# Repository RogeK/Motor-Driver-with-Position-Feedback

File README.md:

# Motor-Driver-with-Position-Feedback
This repo contains a design for a motor driver with position feedback HAT that can be attached to the 40 GPIO pins of the Pi. It is intended to be used to track and control the instantaneous position of the M1N10FB11G Brushless DC Motor which has an incremental encoder attached to its shaft. The scenarios that the daughter board with a Pi are used in include solar tracking systems, automatic sliding gate and a hybrid engine fan.

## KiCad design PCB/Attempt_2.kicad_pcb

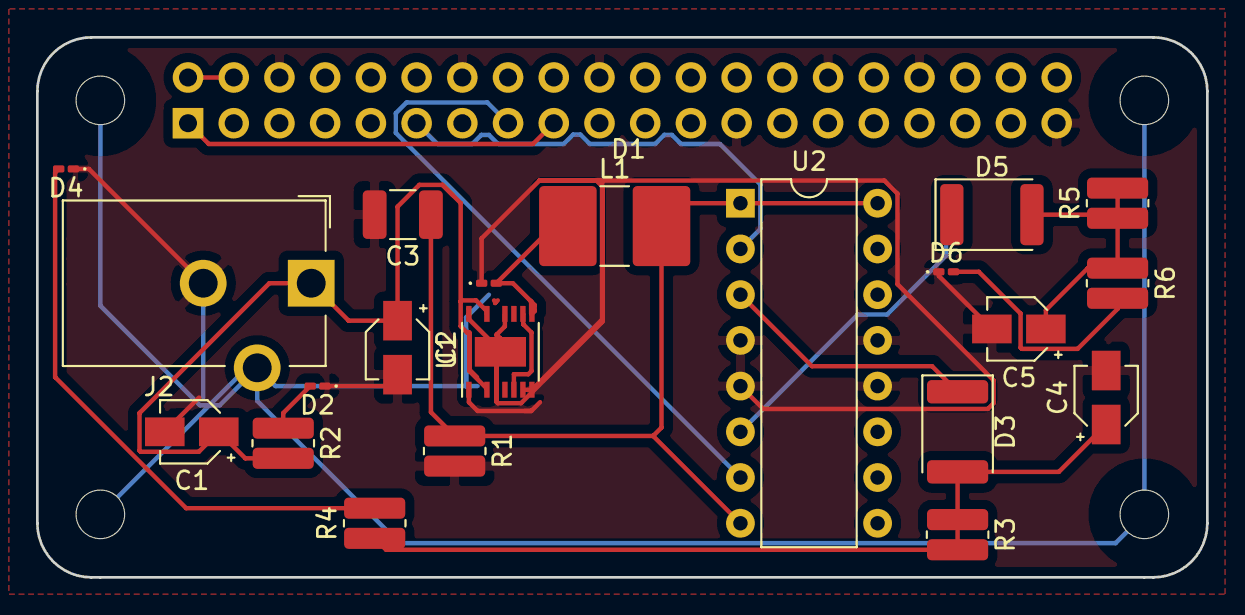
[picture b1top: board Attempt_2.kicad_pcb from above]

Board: 2 copper layers, 65.0 x 30.0 mm, 26 parts (1 on the bottom side), 16 nets.

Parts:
C1, C2: 15uF; CP_Elec_3x5.3
C3: 22u; C_1210_3225Metric_Pad1.33x2.70mm_HandSolder
C4, C5: 4.7u; CP_Elec_3x5.3
D1: DIODE; D_0201_0603Metric_Pad0.64x0.40mm_HandSolder
D2, D4, D6: LED; LED_0201_0603Metric_Pad0.64x0.40mm_HandSolder
D3, D5: DIODE; D_1812_4532Metric_Pad1.30x3.40mm_HandSolder
H1, H2, H3, H4: MountingHole; MountingHole_2.7mm_M2.5_uHAT_RPi
J1: GPIO_CONNECTOR; PinSocket_2x20_P2.54mm_Vertical_Centered_Anchor
J2: Barrel_Jack; BarrelJack_CUI_PJ-102AH_Horizontal
L1: 100u; L_2816_7142Metric_Pad3.20x4.45mm_HandSolder
R1: 13.2; R_0612_1632Metric_Pad1.18x3.40mm_HandSolder
R2: 10k; R_0612_1632Metric_Pad1.18x3.40mm_HandSolder
R3, R5: 3k; R_0612_1632Metric_Pad1.18x3.40mm_HandSolder
R4, R6: 20k; R_0612_1632Metric_Pad1.18x3.40mm_HandSolder
U1: LTC3638; Linear_MSOP-12-16-1EP_3x4mm_P0.5mm
U2: L293D; DIP-16_W7.62mm

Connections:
5Vcc: C3.1, L1.2, R1.1, U2.1, U2.8, U2.16
12Vcc: C1.1, C2.1, J2.1, R2.2, U1.3, U1.14
+3V3: J1.1, J1.17
+5V: J1.2, J1.4
/Led_Status/Motor_Status_Led_1: D3.1, U2.3
/Led_Status/Motor_Status_Led_2: D5.1, U2.6
GND: C1.2, C2.2, C3.2, C4.2, C5.2, D1.1, D2.1, D4.1, D6.1, J1.6, J1.9, J1.14, J1.20, J1.25, J1.30, J1.34, J1.39, J2.2, R1.2, U1.7, U1.8, U1.12, U1.16, U1.17, U2.4, U2.5, U2.12, U2.13
GPIO_17: J1.11, U2.2
GPIO_22: J1.15, U2.7
unnamed: C4.1, D3.2, R3.1, R3.2, R4.1
unnamed: C5.1, D5.2, R5.1, R5.2, R6.1
unnamed: D1.2, L1.1, U1.1, U1.9
unnamed: D2.2, R2.1
unnamed: D4.2, R4.2
unnamed: D6.2, R6.2
unnamed: U1.6, U1.10

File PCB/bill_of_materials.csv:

Bill Of Materials,,,
"Id;""Designator"";""Package"";""Quantity"";""Designation"";""Supplier and ref"";",,,
"1;""J1"";""PinSocket_2x20_P2.54mm_Vertical_Centered_Anchor"";1;""GPIO_CONNECTOR"";;;",,,
"2;""H1",H2,H3,"H4"";""MountingHole_2.7mm_M2.5_uHAT_RPi"";4;""MountingHole"";;;"
"3;""C3"";""C_1210_3225Metric_Pad1.33x2.70mm_HandSolder"";1;""22u"";;;",,,
"4;""D1"";""D_0201_0603Metric_Pad0.64x0.40mm_HandSolder"";1;""DIODE"";;;",,,
"5;""J2"";""BarrelJack_CUI_PJ-102AH_Horizontal"";1;""Barrel_Jack"";;;",,,
"6;""L1"";""L_2816_7142Metric_Pad3.20x4.45mm_HandSolder"";1;""100u"";;;",,,
"7;""R1"";""R_0612_1632Metric_Pad1.18x3.40mm_HandSolder"";1;""13.2"";;;",,,
"8;""R2"";""R_0612_1632Metric_Pad1.18x3.40mm_HandSolder"";1;""10k"";;;",,,
"9;""R3","R5"";""R_0612_1632Metric_Pad1.18x3.40mm_HandSolder"";2;""3k"";;;",,
"10;""R4","R6"";""R_0612_1632Metric_Pad1.18x3.40mm_HandSolder"";2;""20k"";;;",,
"11;""U1"";""Linear_MSOP-12-16-1EP_3x4mm_P0.5mm"";1;""LTC3638"";;;",,,
"12;""U2"";""DIP-16_W7.62mm"";1;""L293D"";;;",,,
"13;""C1","C2"";""CP_Elec_3x5.3"";2;""15uF"";;;",,
"14;""C4","C5"";""CP_Elec_3x5.3"";2;""4.7u"";;;",,
"15;""D2",D4,"D6"";""LED_0201_0603Metric_Pad0.64x0.40mm_HandSolder"";3;""LED"";;;",
"16;""D3","D5"";""D_1812_4532Metric_Pad1.30x3.40mm_HandSolder"";2;""DIODE"";;;",,

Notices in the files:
PCB/Attempt_2.kicad_pcb:
This PCB design is licensed under MIT Open Source License.
